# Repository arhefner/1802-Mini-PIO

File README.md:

# 1802-Mini-PIO
Parallel Expansion Board for the 1802/Mini Computer

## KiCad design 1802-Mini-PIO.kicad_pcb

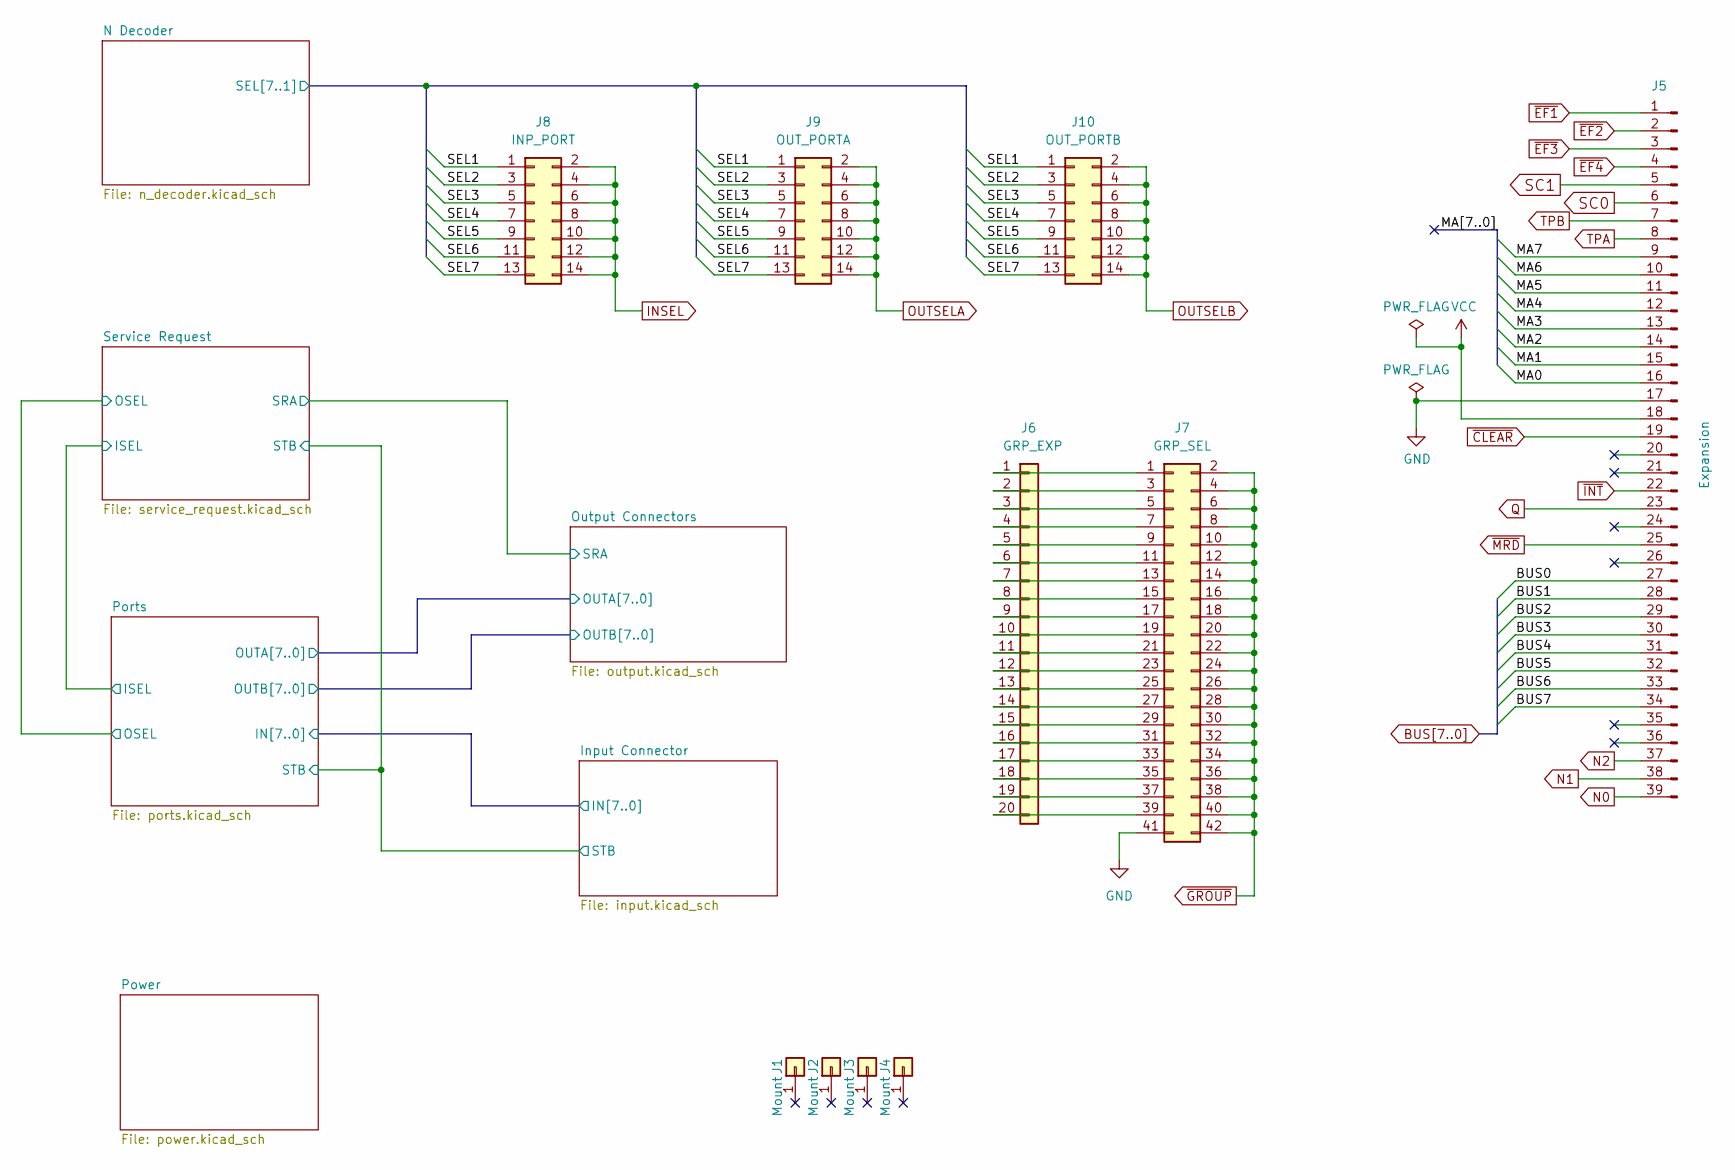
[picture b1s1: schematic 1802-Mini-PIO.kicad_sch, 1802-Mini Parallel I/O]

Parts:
J1, J2, J3, J4: Mount; 1pin
J5: Expansion; Pin_Header_Straight_1x39_Pitch2.54mm
J6: GRP_EXP; PinHeader_1x20_P2.54mm_Vertical
J7: GRP_SEL; PinHeader_2x21_P2.54mm_Vertical
J8: INP_PORT; PinHeader_2x07_P2.54mm_Vertical
J9: OUT_PORTA; PinHeader_2x07_P2.54mm_Vertical
J10: OUT_PORTB; PinHeader_2x07_P2.54mm_Vertical

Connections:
/MA0: J5.16
/MA1: J5.15
/MA2: J5.14
/MA3: J5.13
/MA4: J5.12
/MA5: J5.11
/MA6: J5.10
/MA7: J5.9
/N Decoder/SEL1: J8.1, J9.1, J10.1; also elsewhere on the board
/N Decoder/SEL2: J8.3, J9.3, J10.3; also elsewhere on the board
/N Decoder/SEL3: J8.5, J9.5, J10.5; also elsewhere on the board
/N Decoder/SEL4: J8.7, J9.7, J10.7; also elsewhere on the board
/N Decoder/SEL5: J8.9, J9.9, J10.9; also elsewhere on the board
/N Decoder/SEL6: J8.11, J9.11, J10.11; also elsewhere on the board
/N Decoder/SEL7: J8.13, J9.13, J10.13; also elsewhere on the board
BUS0: J5.27; also elsewhere on the board
BUS1: J5.28; also elsewhere on the board
BUS2: J5.29; also elsewhere on the board
BUS3: J5.30; also elsewhere on the board
BUS4: J5.31; also elsewhere on the board
BUS5: J5.32; also elsewhere on the board
BUS6: J5.33; also elsewhere on the board
BUS7: J5.34; also elsewhere on the board
INSEL: J8.2, J8.4, J8.6, J8.8, J8.10, J8.12, J8.14; also elsewhere on the board
N0: J5.39; also elsewhere on the board
N1: J5.38; also elsewhere on the board
N2: J5.37; also elsewhere on the board
unnamed: J6.1, J7.1
unnamed: J6.2, J7.3
unnamed: J6.3, J7.5
unnamed: J6.4, J7.7
unnamed: J6.5, J7.9
unnamed: J6.6, J7.11
unnamed: J6.7, J7.13
unnamed: J6.8, J7.15
unnamed: J6.9, J7.17
unnamed: J6.10, J7.19
unnamed: J6.11, J7.21
unnamed: J6.12, J7.23
unnamed: J6.13, J7.25
unnamed: J6.14, J7.27
unnamed: J6.15, J7.29
unnamed: J6.16, J7.31
unnamed: J6.17, J7.33
unnamed: J6.18, J7.35
unnamed: J6.19, J7.37
unnamed: J6.20, J7.39
OUTSELA: J9.2, J9.4, J9.6, J9.8, J9.10, J9.12, J9.14; also elsewhere on the board
OUTSELB: J10.2, J10.4, J10.6, J10.8, J10.10, J10.12, J10.14; also elsewhere on the board
Q: J5.23; also elsewhere on the board
SC0: J5.6; also elsewhere on the board
SC1: J5.5; also elsewhere on the board
TPA: J5.8; also elsewhere on the board
TPB: J5.7; also elsewhere on the board
~CLEAR: J5.19; also elsewhere on the board
~EF1: J5.1; also elsewhere on the board
~EF2: J5.2; also elsewhere on the board
~EF3: J5.3; also elsewhere on the board
~EF4: J5.4; also elsewhere on the board
~GROUP: J7.2, J7.4, J7.6, J7.8, J7.10, J7.12, J7.14, J7.16, J7.18, J7.20, J7.22, J7.24, J7.26, J7.28, J7.30, J7.32, J7.34, J7.36, J7.38, J7.40, J7.42; also elsewhere on the board
~INT: J5.22; also elsewhere on the board
~MRD: J5.25; also elsewhere on the board

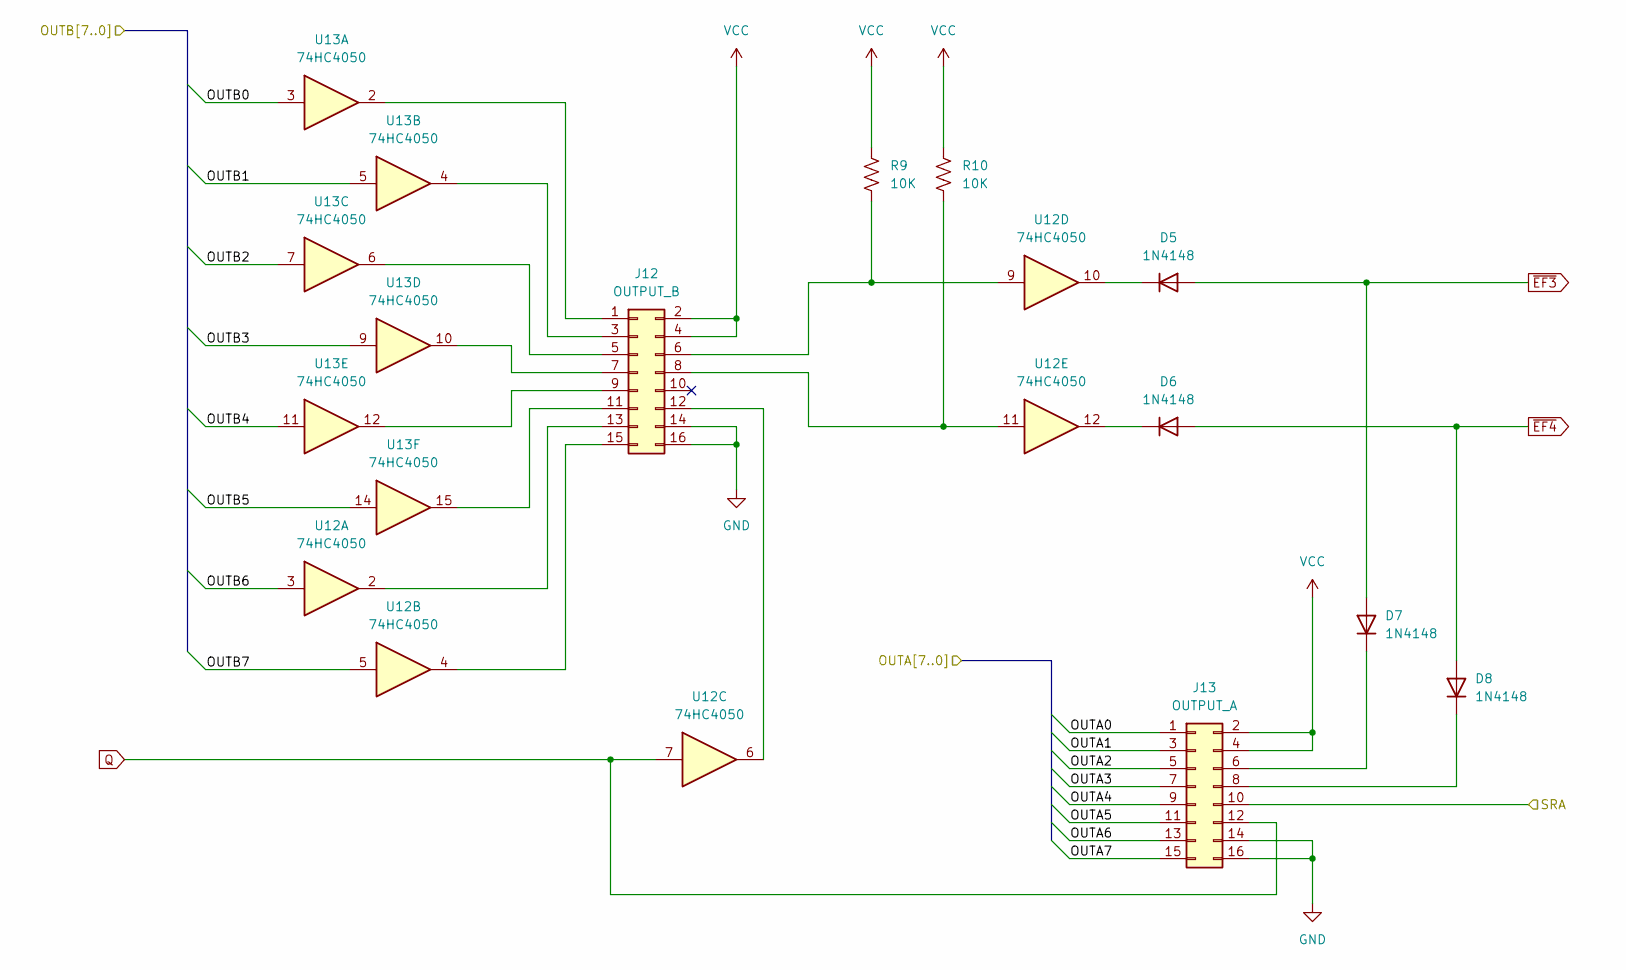
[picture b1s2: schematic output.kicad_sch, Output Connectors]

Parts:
D5, D6, D7, D8: 1N4148; D_DO-35_SOD27_P7.62mm_Horizontal
J12: OUTPUT_B; PinHeader_2x08_P2.54mm_Vertical
J13: OUTPUT_A; PinHeader_2x08_P2.54mm_Vertical
R9, R10: 10K; R_Axial_DIN0207_L6.3mm_D2.5mm_P10.16mm_Horizontal
U12, U13: 74HC4050; DIP-16_W7.62mm_Socket

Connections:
/Output Connectors/OUTA0: J13.1; also elsewhere on the board
/Output Connectors/OUTA1: J13.3; also elsewhere on the board
/Output Connectors/OUTA2: J13.5; also elsewhere on the board
/Output Connectors/OUTA3: J13.7; also elsewhere on the board
/Output Connectors/OUTA4: J13.9; also elsewhere on the board
/Output Connectors/OUTA5: J13.11; also elsewhere on the board
/Output Connectors/OUTA6: J13.13; also elsewhere on the board
/Output Connectors/OUTA7: J13.15; also elsewhere on the board
/Output Connectors/OUTB0: U13.3; also elsewhere on the board
/Output Connectors/OUTB1: U13.5; also elsewhere on the board
/Output Connectors/OUTB2: U13.7; also elsewhere on the board
/Output Connectors/OUTB3: U13.9; also elsewhere on the board
/Output Connectors/OUTB4: U13.11; also elsewhere on the board
/Output Connectors/OUTB5: U13.14; also elsewhere on the board
/Output Connectors/OUTB6: U12.3; also elsewhere on the board
/Output Connectors/OUTB7: U12.5; also elsewhere on the board
/Output Connectors/SRA: J13.10; also elsewhere on the board
unnamed: D5.1 (K), U12.10
unnamed: D6.1 (K), U12.12
unnamed: D7.1 (K), J13.6
unnamed: D8.1 (K), J13.8
unnamed: J12.1, U13.2
unnamed: J12.3, U13.4
unnamed: J12.5, U13.6
unnamed: J12.6, R9.2, U12.9
unnamed: J12.7, U13.10
unnamed: J12.8, R10.2, U12.11
unnamed: J12.9, U13.12
unnamed: J12.11, U13.15
unnamed: J12.12, U12.6
unnamed: J12.13, U12.2
unnamed: J12.15, U12.4
Q: J13.12, U12.7; also elsewhere on the board
~EF3: D5.2 (A), D7.2 (A); also elsewhere on the board
~EF4: D6.2 (A), D8.2 (A); also elsewhere on the board

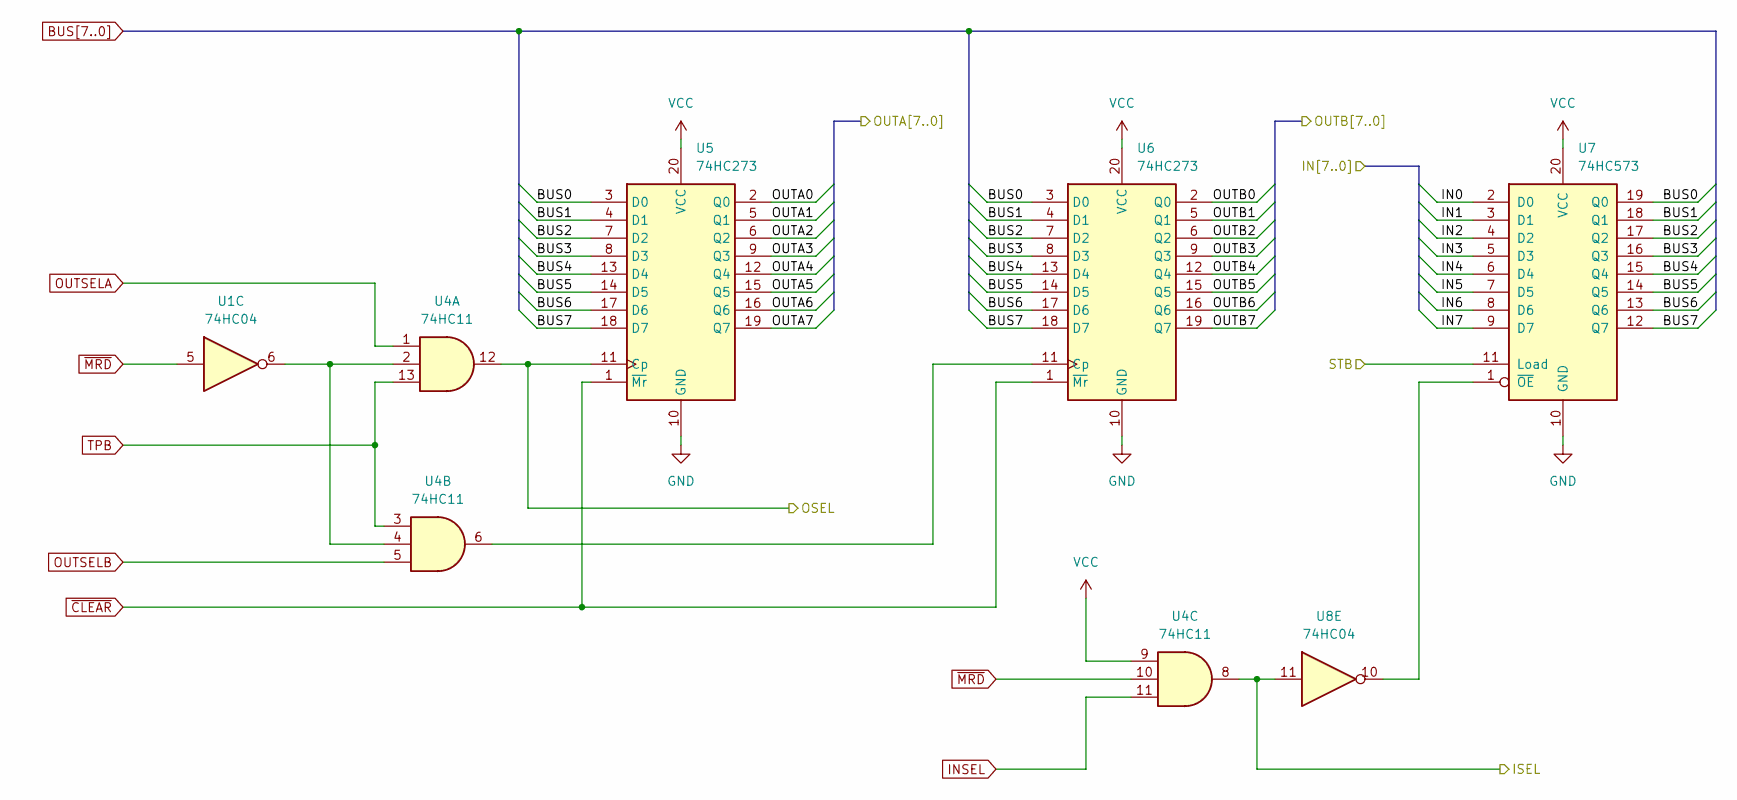
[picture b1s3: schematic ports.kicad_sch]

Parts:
U1, U8: 74HC04; DIP-14_W7.62mm_Socket
U4: 74HC11; DIP-14_W7.62mm_Socket
U5, U6: 74HC273; DIP-20_W7.62mm_Socket
U7: 74HC573; DIP-20_W7.62mm_Socket

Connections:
/Input Connector/IN0: U7.2 (D0); also elsewhere on the board
/Input Connector/IN1: U7.3 (D1); also elsewhere on the board
/Input Connector/IN2: U7.4 (D2); also elsewhere on the board
/Input Connector/IN3: U7.5 (D3); also elsewhere on the board
/Input Connector/IN4: U7.6 (D4); also elsewhere on the board
/Input Connector/IN5: U7.7 (D5); also elsewhere on the board
/Input Connector/IN6: U7.8 (D6); also elsewhere on the board
/Input Connector/IN7: U7.9 (D7); also elsewhere on the board
/Input Connector/STB: U7.11 (Load); also elsewhere on the board
/Output Connectors/OUTA0: U5.2 (Q0); also elsewhere on the board
/Output Connectors/OUTA1: U5.5 (Q1); also elsewhere on the board
/Output Connectors/OUTA2: U5.6 (Q2); also elsewhere on the board
/Output Connectors/OUTA3: U5.9 (Q3); also elsewhere on the board
/Output Connectors/OUTA4: U5.12 (Q4); also elsewhere on the board
/Output Connectors/OUTA5: U5.15 (Q5); also elsewhere on the board
/Output Connectors/OUTA6: U5.16 (Q6); also elsewhere on the board
/Output Connectors/OUTA7: U5.19 (Q7); also elsewhere on the board
/Output Connectors/OUTB0: U6.2 (Q0); also elsewhere on the board
/Output Connectors/OUTB1: U6.5 (Q1); also elsewhere on the board
/Output Connectors/OUTB2: U6.6 (Q2); also elsewhere on the board
/Output Connectors/OUTB3: U6.9 (Q3); also elsewhere on the board
/Output Connectors/OUTB4: U6.12 (Q4); also elsewhere on the board
/Output Connectors/OUTB5: U6.15 (Q5); also elsewhere on the board
/Output Connectors/OUTB6: U6.16 (Q6); also elsewhere on the board
/Output Connectors/OUTB7: U6.19 (Q7); also elsewhere on the board
/Ports/ISEL: U4.8, U8.11; also elsewhere on the board
/Ports/OSEL: U4.12, U5.11 (Cp); also elsewhere on the board
BUS0: U5.3 (D0), U6.3 (D0), U7.19 (Q0); also elsewhere on the board
BUS1: U5.4 (D1), U6.4 (D1), U7.18 (Q1); also elsewhere on the board
BUS2: U5.7 (D2), U6.7 (D2), U7.17 (Q2); also elsewhere on the board
BUS3: U5.8 (D3), U6.8 (D3), U7.16 (Q3); also elsewhere on the board
BUS4: U5.13 (D4), U6.13 (D4), U7.15 (Q4); also elsewhere on the board
BUS5: U5.14 (D5), U6.14 (D5), U7.14 (Q5); also elsewhere on the board
BUS6: U5.17 (D6), U6.17 (D6), U7.13 (Q6); also elsewhere on the board
BUS7: U5.18 (D7), U6.18 (D7), U7.12 (Q7); also elsewhere on the board
INSEL: U4.11; also elsewhere on the board
unnamed: U1.6, U4.2, U4.4
unnamed: U4.6, U6.11 (Cp)
unnamed: U7.1 (~OE), U8.10
OUTSELA: U4.1; also elsewhere on the board
OUTSELB: U4.5; also elsewhere on the board
TPB: U4.3, U4.13; also elsewhere on the board
~CLEAR: U5.1 (~Mr), U6.1 (~Mr); also elsewhere on the board
~MRD: U1.5, U4.10; also elsewhere on the board

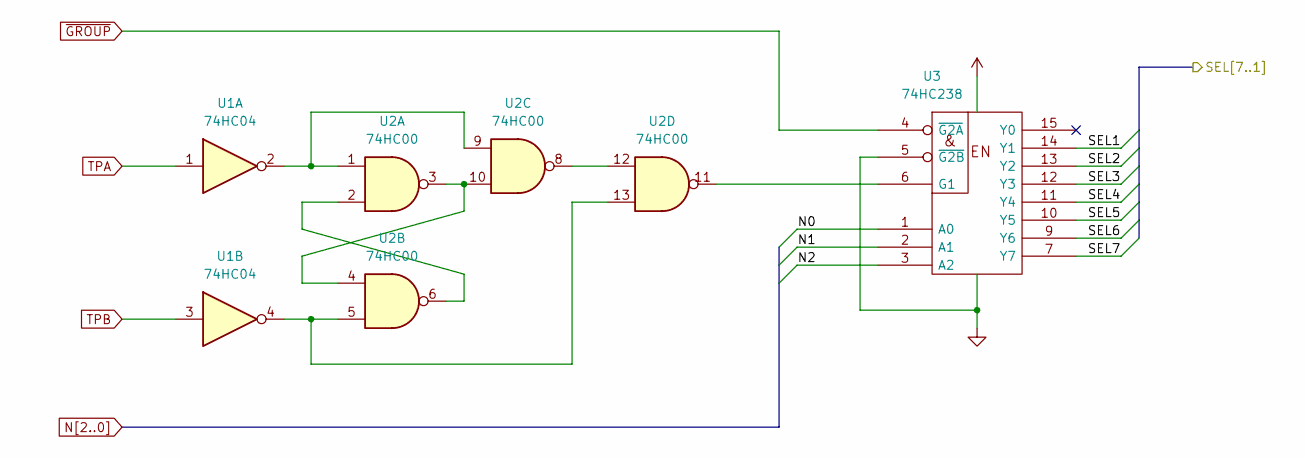
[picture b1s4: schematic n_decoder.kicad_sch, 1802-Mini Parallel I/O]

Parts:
U1: 74HC04; DIP-14_W7.62mm_Socket
U2: 74HC00; DIP-14_W7.62mm_Socket
U3: 74HC238; DIP-16_W7.62mm_Socket

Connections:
/N Decoder/SEL1: U3.14 (Y1); also elsewhere on the board
/N Decoder/SEL2: U3.13 (Y2); also elsewhere on the board
/N Decoder/SEL3: U3.12 (Y3); also elsewhere on the board
/N Decoder/SEL4: U3.11 (Y4); also elsewhere on the board
/N Decoder/SEL5: U3.10 (Y5); also elsewhere on the board
/N Decoder/SEL6: U3.9 (Y6); also elsewhere on the board
/N Decoder/SEL7: U3.7 (Y7); also elsewhere on the board
N0: U3.1 (A0); also elsewhere on the board
N1: U3.2 (A1); also elsewhere on the board
N2: U3.3 (A2); also elsewhere on the board
unnamed: U1.2, U2.1, U2.9
unnamed: U1.4, U2.5, U2.13
unnamed: U2.2, U2.6
unnamed: U2.3, U2.4, U2.10
unnamed: U2.11, U3.6 (G1)
unnamed: U2.8, U2.12
TPA: U1.1; also elsewhere on the board
TPB: U1.3; also elsewhere on the board
~GROUP: U3.4 (~G2A); also elsewhere on the board

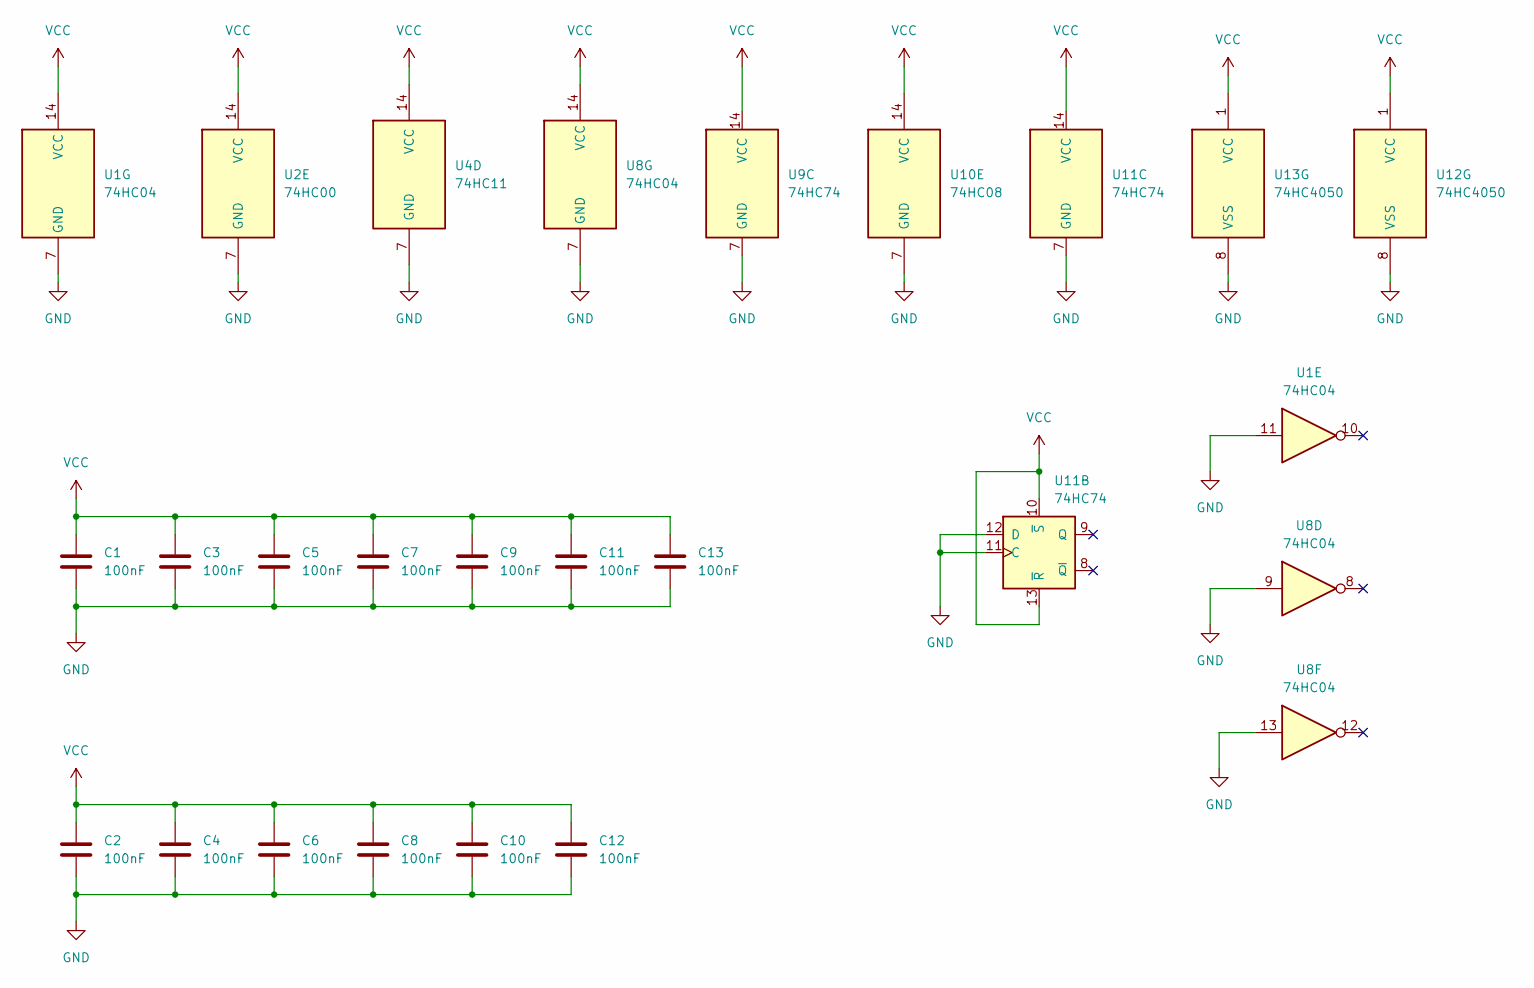
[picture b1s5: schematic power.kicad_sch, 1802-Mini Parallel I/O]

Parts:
C1, C2, C3, C4, C5, C6, C7, C8, C9, C10, C11, C12, C13: 100nF; C_Disc_D4.7mm_W2.5mm_P5.00mm
U1, U8: 74HC04; DIP-14_W7.62mm_Socket
U2: 74HC00; DIP-14_W7.62mm_Socket
U4: 74HC11; DIP-14_W7.62mm_Socket
U9, U11: 74HC74; DIP-14_W7.62mm_Socket
U10: 74HC08; DIP-14_W7.62mm_Socket
U12, U13: 74HC4050; DIP-16_W7.62mm_Socket

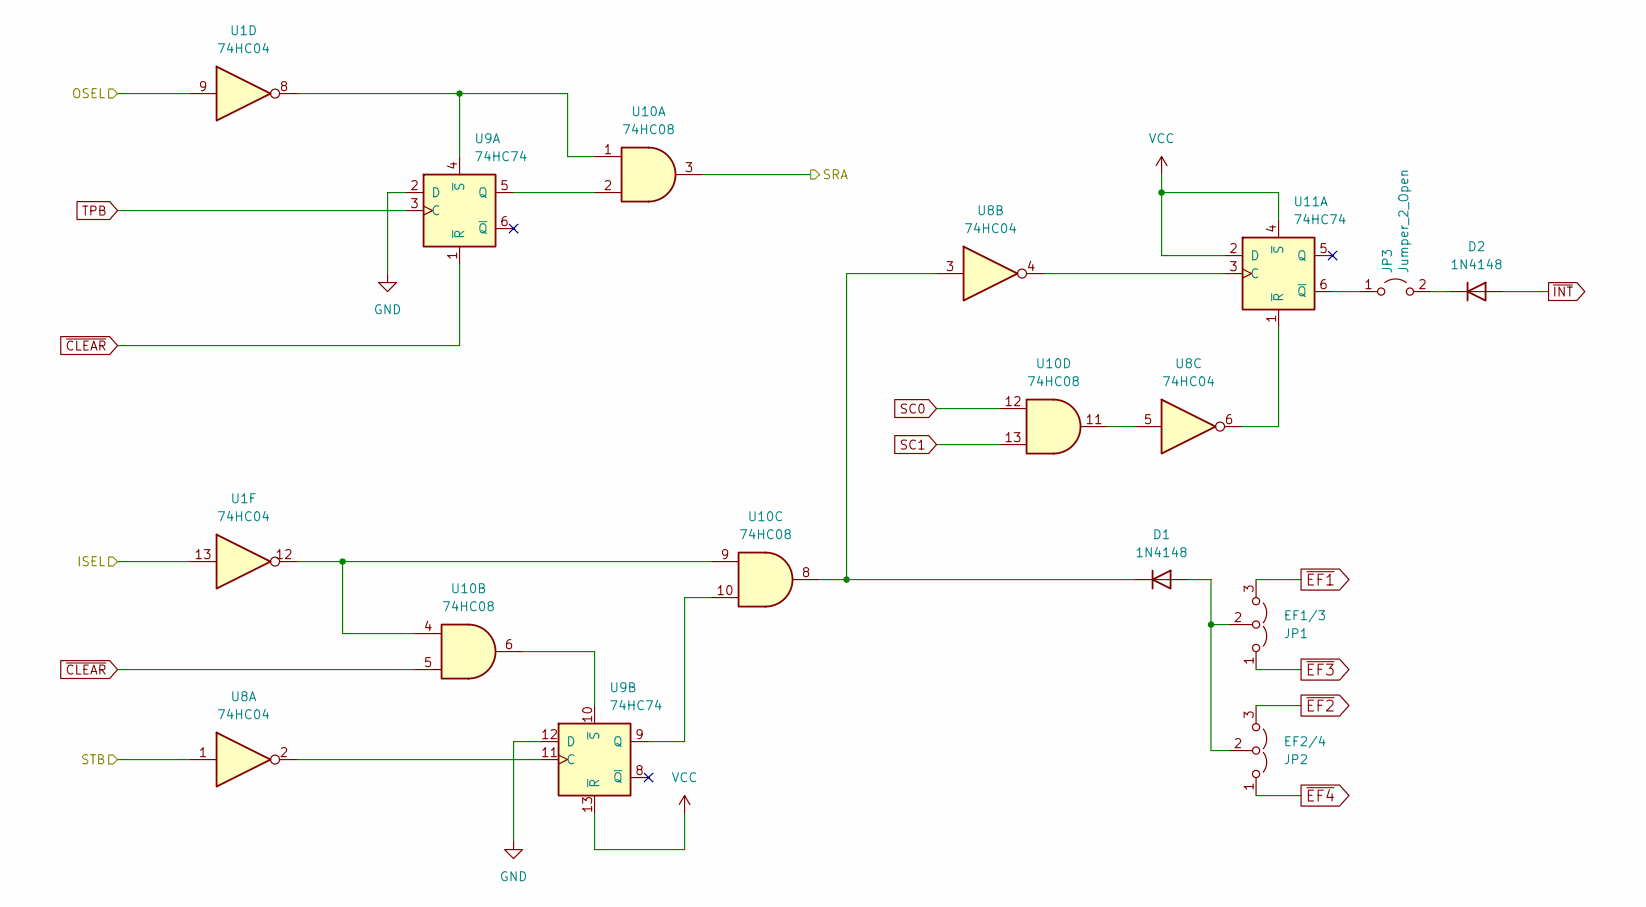
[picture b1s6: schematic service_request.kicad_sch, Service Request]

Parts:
D1, D2: 1N4148; D_DO-35_SOD27_P7.62mm_Horizontal
JP1: EF1/3; PinHeader_1x03_P2.54mm_Vertical
JP2: EF2/4; PinHeader_1x03_P2.54mm_Vertical
JP3: Jumper_2_Open; PinHeader_1x02_P2.54mm_Vertical
U1, U8: 74HC04; DIP-14_W7.62mm_Socket
U9, U11: 74HC74; DIP-14_W7.62mm_Socket
U10: 74HC08; DIP-14_W7.62mm_Socket

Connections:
/Input Connector/STB: U8.1; also elsewhere on the board
/Output Connectors/SRA: U10.3; also elsewhere on the board
/Ports/ISEL: U1.13; also elsewhere on the board
/Ports/OSEL: U1.9; also elsewhere on the board
unnamed: D1.1 (K), U8.3, U10.8
unnamed: D1.2 (A), JP1.2 (C), JP2.2 (C)
unnamed: D2.1 (K), JP3.2 (B)
unnamed: JP3.1 (A), U11.6 (~Q)
unnamed: U1.8, U9.4 (~S), U10.1
unnamed: U1.12, U10.4, U10.9
unnamed: U8.2, U9.11 (C)
unnamed: U9.5 (Q), U10.2
unnamed: U9.10 (~S), U10.6
unnamed: U9.9 (Q), U10.10
unnamed: U8.5, U10.11
unnamed: U8.6, U11.1 (~R)
unnamed: U8.4, U11.3 (C)
SC0: U10.12; also elsewhere on the board
SC1: U10.13; also elsewhere on the board
TPB: U9.3 (C); also elsewhere on the board
~CLEAR: U9.1 (~R), U10.5; also elsewhere on the board
~EF1: JP1.3 (B); also elsewhere on the board
~EF2: JP2.3 (B); also elsewhere on the board
~EF3: JP1.1 (A); also elsewhere on the board
~EF4: JP2.1 (A); also elsewhere on the board
~INT: D2.2 (A); also elsewhere on the board

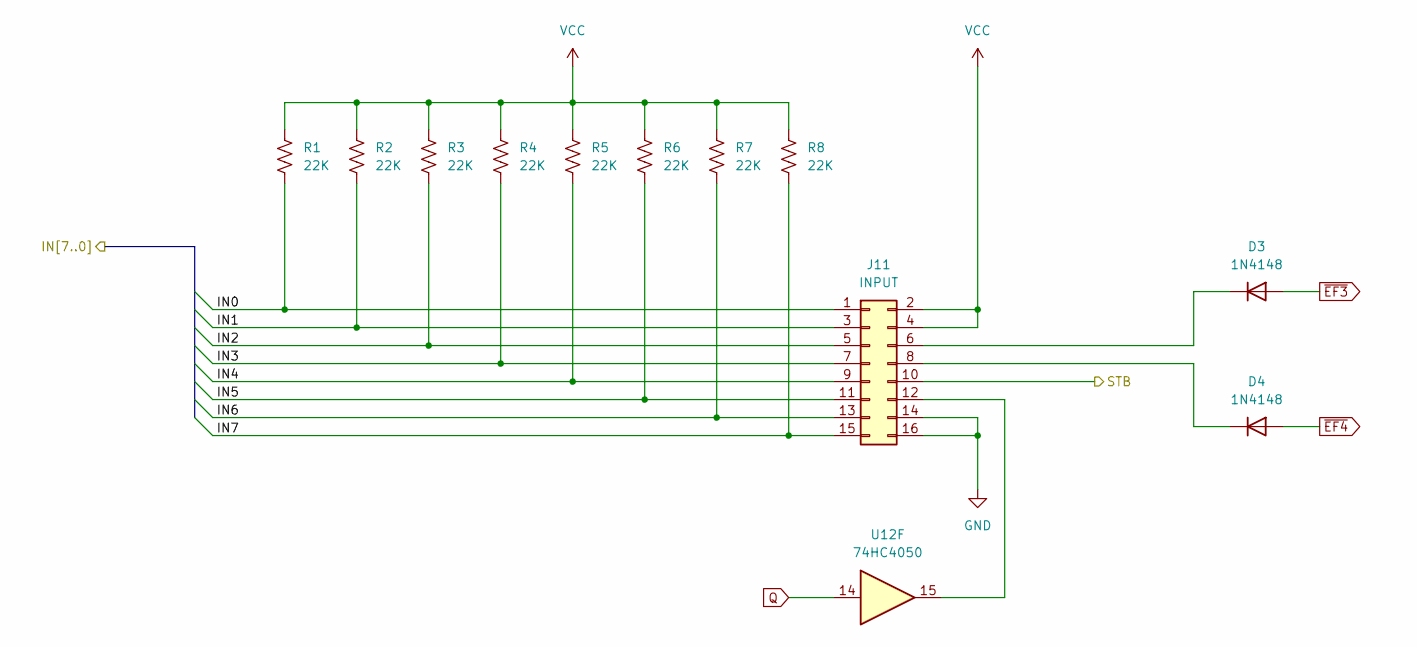
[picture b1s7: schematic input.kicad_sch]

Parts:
D3, D4: 1N4148; D_DO-35_SOD27_P7.62mm_Horizontal
J11: INPUT; PinHeader_2x08_P2.54mm_Vertical
R1, R2, R3, R4, R5, R6, R7, R8: 22K; R_Axial_DIN0207_L6.3mm_D2.5mm_P10.16mm_Horizontal
U12: 74HC4050; DIP-16_W7.62mm_Socket

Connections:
/Input Connector/IN0: J11.1, R1.2; also elsewhere on the board
/Input Connector/IN1: J11.3, R2.2; also elsewhere on the board
/Input Connector/IN2: J11.5, R3.2; also elsewhere on the board
/Input Connector/IN3: J11.7, R4.2; also elsewhere on the board
/Input Connector/IN4: J11.9, R5.2; also elsewhere on the board
/Input Connector/IN5: J11.11, R6.2; also elsewhere on the board
/Input Connector/IN6: J11.13, R7.2; also elsewhere on the board
/Input Connector/IN7: J11.15, R8.2; also elsewhere on the board
/Input Connector/STB: J11.10; also elsewhere on the board
unnamed: D3.1 (K), J11.6
unnamed: D4.1 (K), J11.8
unnamed: J11.12, U12.15
Q: U12.14; also elsewhere on the board
~EF3: D3.2 (A); also elsewhere on the board
~EF4: D4.2 (A); also elsewhere on the board

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
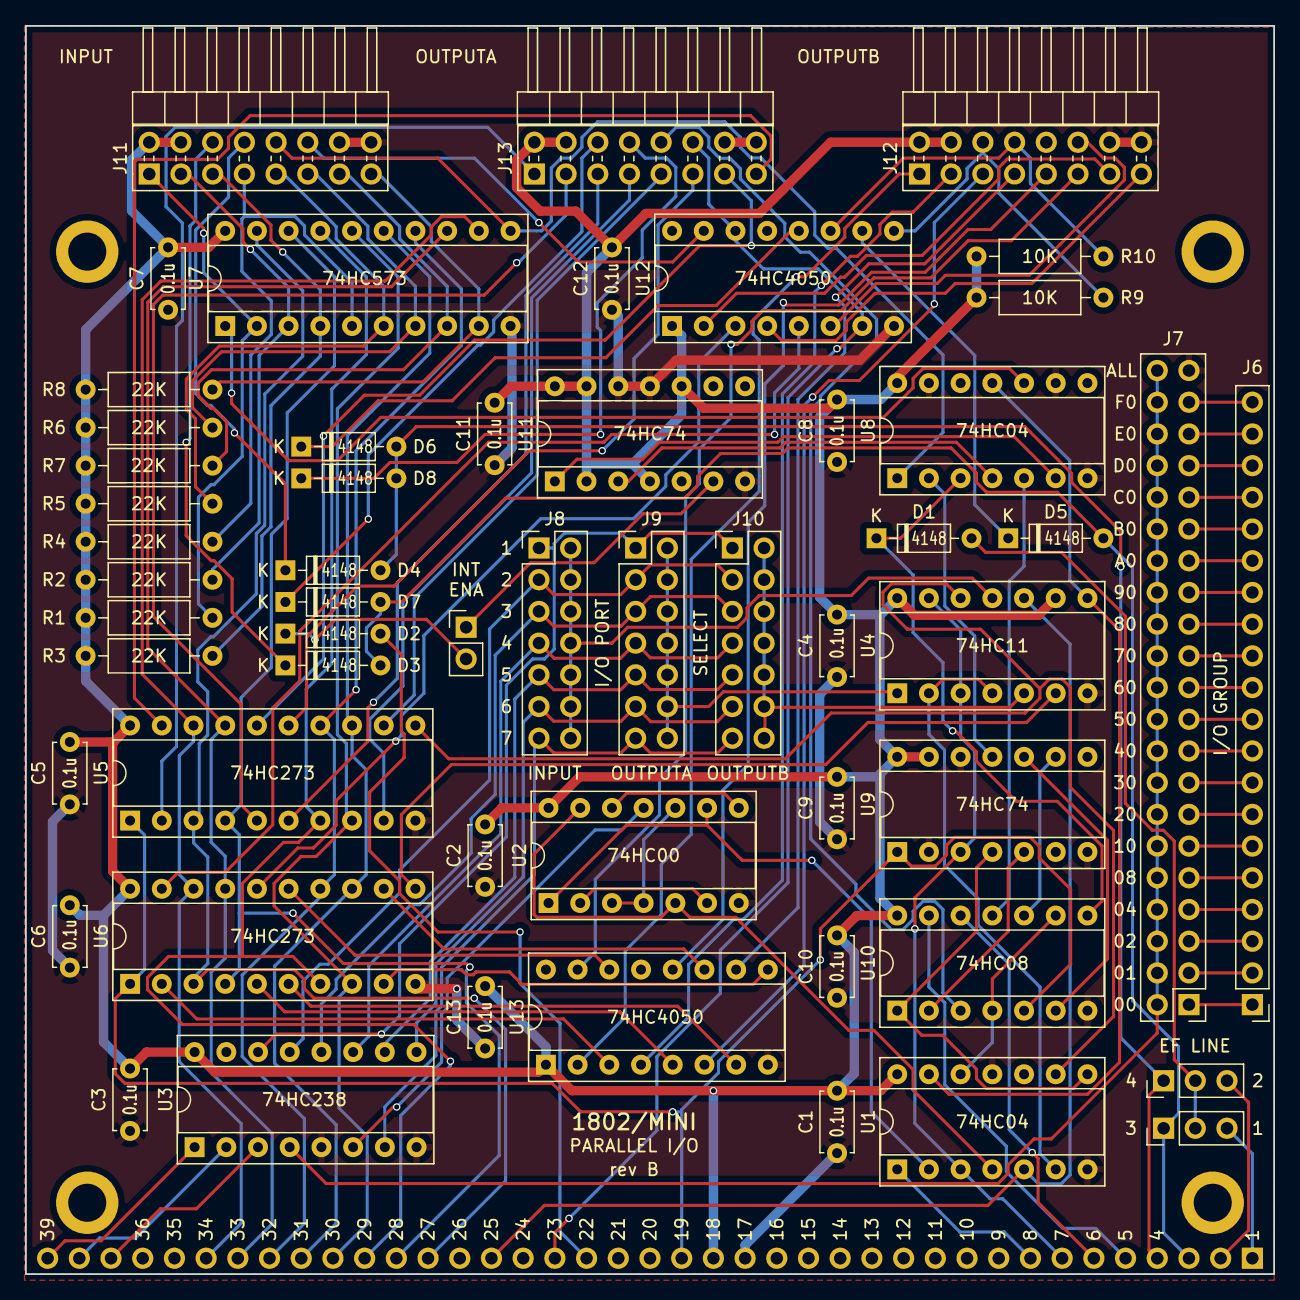
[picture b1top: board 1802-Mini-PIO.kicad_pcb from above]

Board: 2 copper layers, 100.0 x 100.0 mm, 60 parts (0 on the bottom side), 124 nets.

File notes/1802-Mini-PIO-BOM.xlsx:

Please refer to these notes as applicable for the parts list below:
*A | The Samtec 39 pin connector, when ordering from Digikey, will always show zero 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
*B | These parts may be omitted if group port selection will not be used. See assemb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
*C | Use the long tail headers for stacked assembly, and the right-angle headers if 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
PARALLEL INTERFACE
Qty | Description |  | Manufacturer | Manufacturer # | Vendor | Vendor # | Price | Qty | Total
Integrated Circuits
2 | 74HC04 | U1,U8 | TI | SN74HC04N | Mouser | 595-SN74HC04N | 0.62 | 2 | 1.24
1 | 74HC00 | U2 | TI | SN74HC00N | Mouser | 595-SN74HC00N | 0.6 | 1 | 0.6
1 | 74HC238 | U3 | TI | CD74HC238E | Mouser | 595-CD74HC238E | 0.7 | 1 | 0.7
1 | 74HC11 | U4 | TI | SN74HC11N | Mouser | 595-SN74HC11N | 0.6 | 1 | 0.6
2 | 74HC273 | U5,U6 | TI | SN74HC273N | Mouser | 595-SN74HC273N | 0.93 | 2 | 1.86
1 | 74HC573 | U7 | TI | SN74HC573AN | Mouser | 595-SN74HC573AN | 0.94 | 1 | 0.94
2 | 74HC74 | U9,U11 | TI | SN74HC74N | Mouser | 595-SN74HC74N | 0.6 | 2 | 1.2
1 | 74HC08 | U10 | TI | SN74HC08N | Mouser | 595-SN74HC08N | 0.6 | 1 | 0.6
2 | 74HC4050 | U12,U13 | TI | CD74HC4050E | Mouser | 595-CD74HC4050E | 0.67 | 2 | 1.34
Discrete Components
8 | Diode 1N4148 | D1-D8 | ON Semi | 1N4148 | Mouser | 512-1N4148 | 0.1 | 8 | 0.8
13 | Ceramic capacitor 0.1uF radial 0.2" | C1-13 | Vishay | K104K10X7RF5UH5 | Digikey | BC2665CT-ND | 0.156 | 13 | 2.028
8 | Resistor 1/4 watt 22K | R1-R8 | Stackpole | CF14JT22K0 | Digikey | CF14JT22K0CT-ND | 0.1 | 8 | 0.8
2 | Resistor 1/4 watt 10K | R9,R10 | Stackpole | CF14JT10K0 | Digikey | CF14JT10K0CT-ND | 0.1 | 2 | 0.2
Interconnects
3 | R/A shrouded header 16 pins 0.1" | J11,J12,J13 | Hirose | HIF3FC-16PA-2.54DS(71) | Mouser | 798-HIF3FC16PA254DS1 | 2.5 | 3 | 7.5
2 | Straight header 3 pins 0.1" | JP1,JP2 | Sullins | PREC003SAAN-RC | Digikey | S1012EC-03-ND | 0.09 | 2 | 0.18
1 | Straight header 2 pins 0.1" | JP3 | Sullins | PREC002SAAN-RC | Digikey | S1012EC-02-ND | 0.06 | 1 | 0.06
1 | Straight dual row header 21 position (*B) | J7 | Sullins | PREC021DAAN-RC | Digikey | S2012EC-21-ND | 0.73 | 1 | 0.73
3 | Straight dual row header 7 position | J8,J9,J10 | Sullins | PREC007DAAN-RC | Digikey | S2012EC-07-ND | 0.31 | 3 | 0.92999999999999994
5 | Jumper shunts 0.1" |  | Sullins | STC02SYAN | Digikey | S9000-ND | 0.09 | 5 | 0.44999999999999996
1 | Socket 39 pin 0.1" long tail (*A)(*C) | J5 | Samtec | SSQ-139-03-T-S | Digikey | SAM1206-39-ND | 6.47 | 1 | 6.47
1 | Socket 20 pin 0.1" long tail (*B)(*C) | J6 | Samtec | SSQ-120-03-T-S | Digikey | SAM1206-20-ND | 3.46 | 1 | 3.46
1 | R/A header 39 pin 0.1" (*C) | J5 | Sullins | PREC039SBAN-M71RC | Digikey | S1112EC-39-ND | 0.88 | 1 | 0.88
1 | R/A header 20 pin 0.1" (*C) | J6 | Sullins | PREC020SBAN-M71RC | Digikey | S1112EC-20-ND | 0.5 | 1 | 0.5
Sockets
7 | DIP socket 14 pin 0.3" |  | On Shore | ED14DT | Digikey | ED3045-5-ND | 0.19 | 7 | 1.33
3 | DIP socket 16 pin 0.3" |  | On Shore | ED16DT | Digikey | ED3046-5-ND | 0.26 | 3 | 0.78
3 | DIP socket 20 pin 0.3" |  | On Shore | ED20DT | Digikey | ED3054-5-ND | 0.31 | 3 | 0.92999999999999994
Mechanical
4 | 0.5 inch standoff spacer |  | RAF | 4505-440-AL-7 | Jameco | 393474 | 0.49 | 4 | 1.96
1 | Circuit Board |  | Hefner |  | JLCPCB |  | 0.4 | 1 | 0.4
 |  |  |  |  |  |  | Total |  | 39.467999999999996

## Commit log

2022-12-29 Add project files
2022-12-29 Add pdf of schematic to notes
2023-01-01 Finish Rev A board layout
2023-01-01 Remove backup folder
2023-01-06 Add BOM to notes
2023-04-30 Remove backups from source control.
2023-04-30 Update to Rev B.
2023-05-25 Update pdf schematic to Rev B
